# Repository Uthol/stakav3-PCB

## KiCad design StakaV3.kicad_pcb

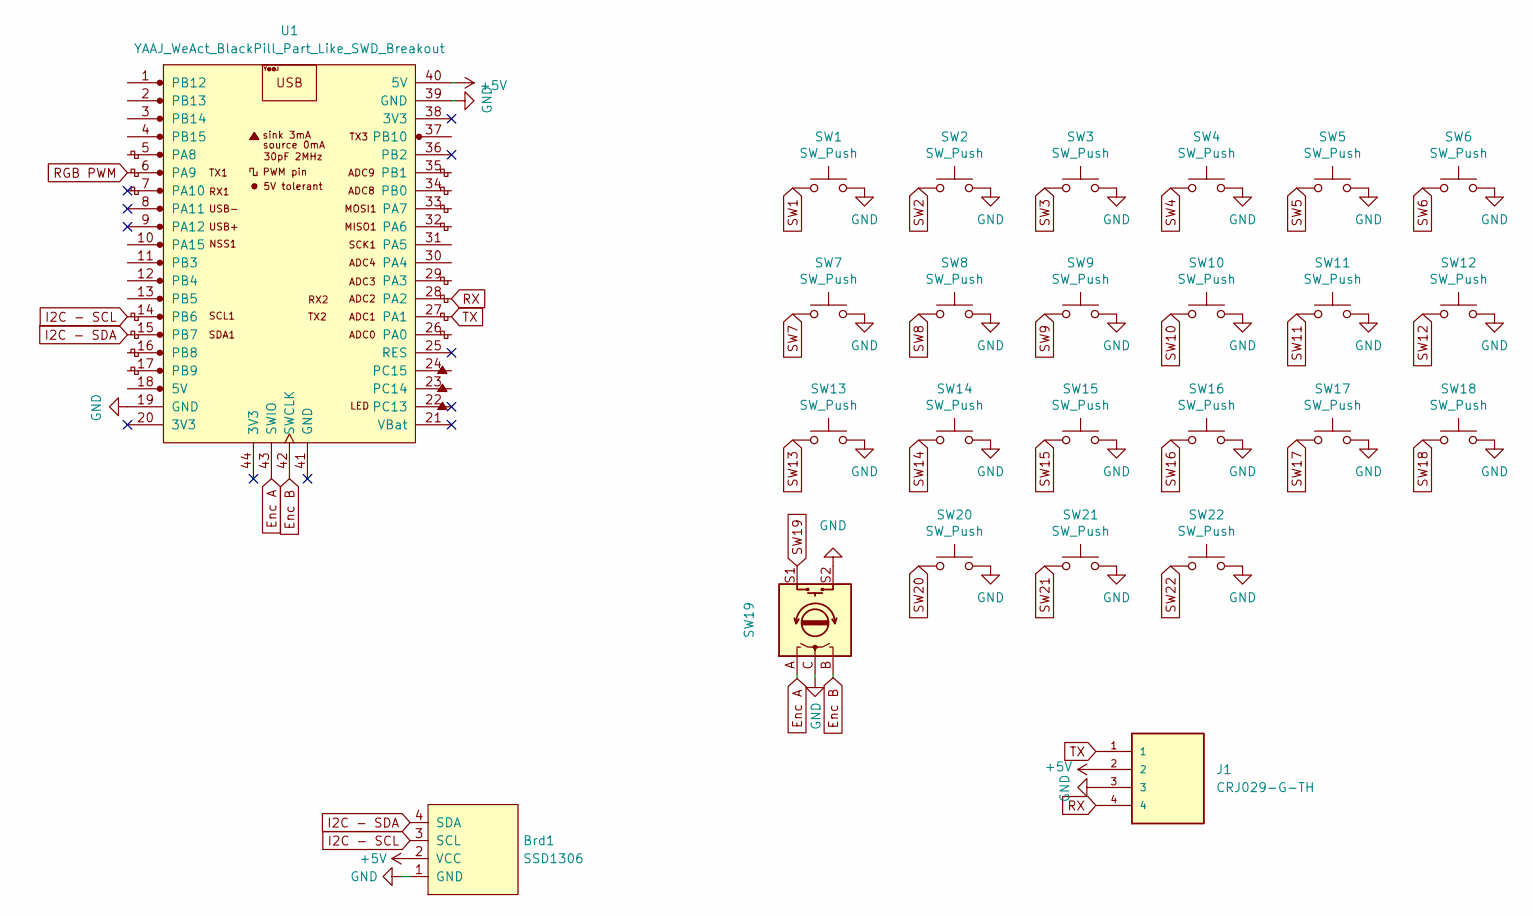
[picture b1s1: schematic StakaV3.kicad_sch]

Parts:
Brd1: SSD1306; 128x64OLED_Pins
J1: CRJ029-G-TH; CUI_CRJ029-G-TH; PARTREV 1.0
SW1, SW2, SW3, SW4, SW5, SW6, SW7, SW8, SW9, SW10, SW11, SW12, SW13, SW14, SW15, SW16, SW17, SW18, SW20, SW21, SW22: SW_Push; SW_MX_reversible
SW19: Rotary_Encoder_Switch; MX_ALPS_PG1350_Rotary
U1: YAAJ_WeAct_BlackPill_Part_Like_SWD_Breakout; BlackPillFlipFlop

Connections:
+5V: Brd1.2 (VCC), J1.2, U1.40 (5V)
Enc A: SW19.A, U1.43 (SWIO)
Enc B: SW19.B, U1.42 (SWCLK)
GND: Brd1.1 (GND), J1.3, SW1.2, SW2.2, SW3.2, SW4.2, SW5.2, SW6.2, SW7.2, SW8.2, SW9.2, SW10.2, SW11.2, SW12.2, SW13.2, SW14.2, SW15.2, SW16.2, SW17.2, SW18.2, SW19.C, SW19.S2, SW20.2, SW21.2, SW22.2, U1.19 (GND), U1.39 (GND)
I2C - SCL: Brd1.3 (SCL), U1.14 (PB6)
I2C - SDA: Brd1.4 (SDA), U1.15 (PB7)
RGB PWM: U1.6 (PA9)
RX: J1.4, U1.28 (PA2)
SW1: SW1.1
SW2: SW2.1
SW3: SW3.1
SW4: SW4.1
SW5: SW5.1
SW6: SW6.1
SW7: SW7.1
SW8: SW8.1
SW9: SW9.1
SW10: SW10.1
SW11: SW11.1
SW12: SW12.1
SW13: SW13.1
SW14: SW14.1
SW15: SW15.1
SW16: SW16.1
SW17: SW17.1
SW18: SW18.1
SW19: SW19.S1
SW20: SW20.1
SW21: SW21.1
SW22: SW22.1
TX: J1.1, U1.27 (PA1)

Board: 2 copper layers, 25 parts (0 on the bottom side), 8 nets, no tracks yet.

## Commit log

2022-12-15 Basic layout
